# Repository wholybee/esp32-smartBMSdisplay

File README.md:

# esp32-smartBMSdisplay
ESP32 version of JBD BMS display with Bluetooth connection

This is a BMS monitor for JBD and Overkill Solar BMS. It supports bluetooth connection to the BMS, and can alarm prior to BMS disconnect per ABYC recommendation. It is inspired by a project at https://github.com/vagueDirector/ArduinoXiaoxiangSmartBMSDisplay, but bears little resemblance at this point.

This project uses the Overkill Solar library for accessing the BMS, and modifiyed code from https://github.com/avinabmalla/ESP32_BleSerial

I used an ESP32-WROOM. Others might work also. BLE enabled Arduinos will not work. The ESP32 will connect to the first BMS it finds via bluetooth. Button one cycles through screens, and button two silences the alarm if it is triggered.

To use the alarm requires some changes in the BMS programming. There is a parameter for the delay in seconds before the cutoff occurs. Normally this is set very small, to 1 or 2 seconds. This value is how long of a warning you will get before the cutoff occurs. Some versions of the app do not allow this to be set greater than 10 seconds, but using the Overkill Solar app allows higher values.

Care should be taken when selecting the delay value. If an overvoltage or undervoltage situation occurs, there should be no issue waiting 20 or 30 seconds. If an overcurrent situation occurs, you really should not wait to disconnect to allow for an alarm, regardless of what ABYC says. So, I suggest leaving the delay for overcurrent very low, and changing the delay for overvoltage to 20 or 30 seconds.

ESP32 WROOM - https://www.amazon.com/gp/product/B08MQDS6WV/ref=ppx_yo_dt_b_search_asin_title
128x64 OLED screen - https://www.amazon.com/gp/product/B08BRCBKNR/ref=ppx_yo_dt_b_asin_title_o01_s00
Button - https://www.digikey.com/en/products/detail/c-k/KSA0A531-LFTR/5975610?s=N4IgTCBcDaINIGUCCAGJBWAzARgDIDEAVAJQFoA5AERAF0BfIA
Button cap - https://www.digikey.com/en/products/detail/c-k/BTNK0120/498768?s=N4IgTCBcDaICwAYCMBaJYDMBOFA5AIiALoC%2BQA
Buzzer - https://www.amazon.com/gp/product/B07TRK5M2T/ref=ppx_yo_dt_b_search_asin_title

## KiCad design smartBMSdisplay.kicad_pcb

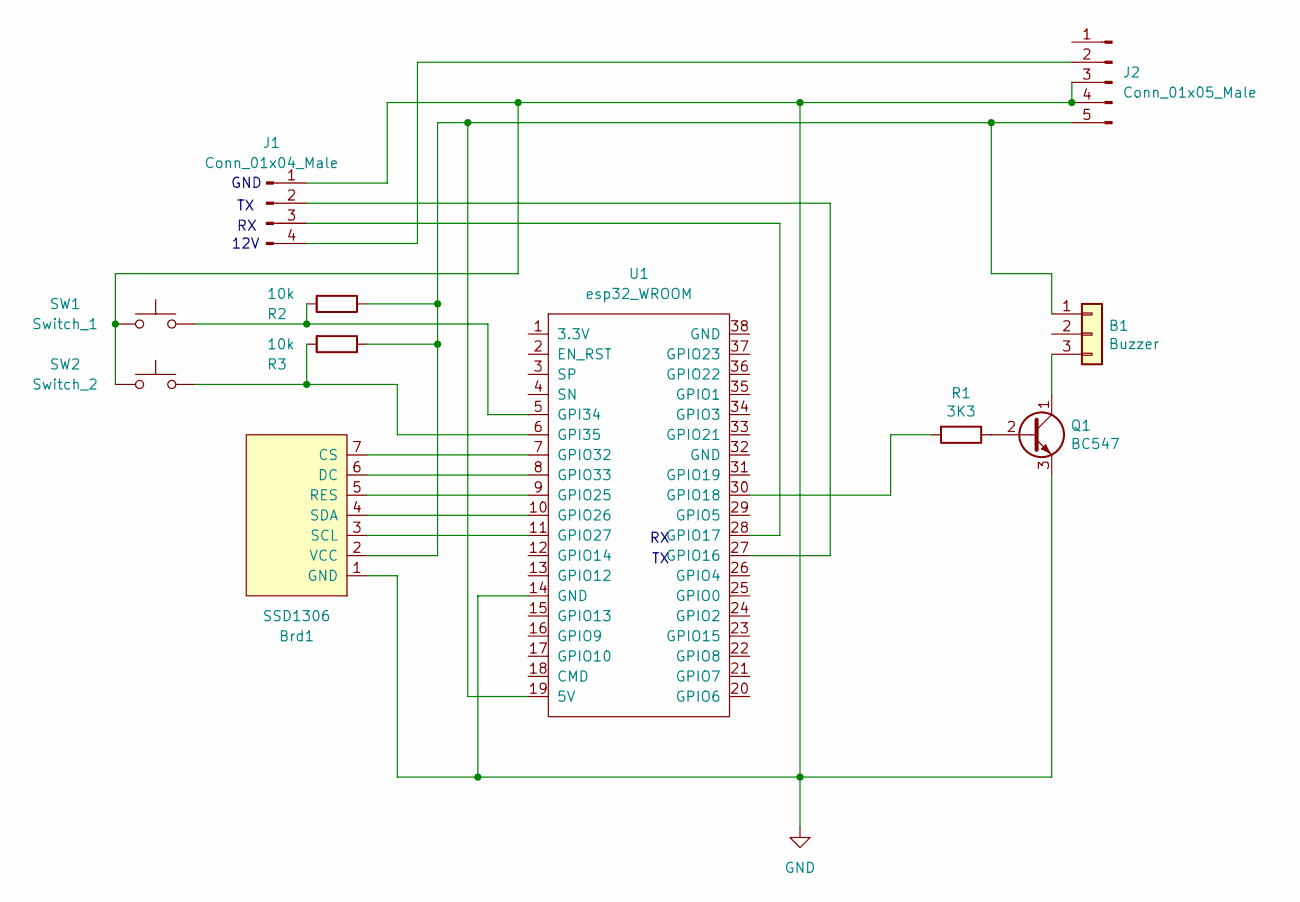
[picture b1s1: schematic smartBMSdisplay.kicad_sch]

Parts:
B1: Buzzer; PinHeader_1x03_P2.00mm_Vertical
Brd1: SSD1306; 128x64OLED
J1: Conn_01x04_Male; PinHeader_1x04_P2.54mm_Vertical
J2: Conn_01x05_Male; PinHeader_1x05_P2.54mm_Vertical
Q1: BC547; TO-92_HandSolder
R1: 3K3; R_Axial_DIN0207_L6.3mm_D2.5mm_P10.16mm_Horizontal
R2, R3: 10k; R_Axial_DIN0207_L6.3mm_D2.5mm_P10.16mm_Horizontal
SW1: Switch_1; SW_Tactile_Straight_KSA0Axx1LFTR
SW2: Switch_2; SW_Tactile_Straight_KSA0Axx1LFTR
U1: esp32_WROOM; ESP32_Devkit_38Pins

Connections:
GND: Brd1.1 (GND), J1.1, J2.3, J2.4, Q1.3 (E), SW1.2, SW2.2, U1.14 (GND)
unnamed: B1.1, Brd1.2 (VCC), J2.5, R2.1, R3.1, U1.19 (5V)
unnamed: B1.3, Q1.1 (C)
unnamed: Brd1.3 (SCL), U1.11 (GPIO27)
unnamed: Brd1.4 (SDA), U1.10 (GPIO26)
unnamed: Brd1.5 (RES), U1.9 (GPIO25)
unnamed: Brd1.6 (DC), U1.8 (GPIO33)
unnamed: Brd1.7 (CS), U1.7 (GPIO32)
unnamed: J1.2, U1.27 (GPIO16)
unnamed: J1.3, U1.28 (GPIO17)
unnamed: J1.4, J2.2
unnamed: Q1.2 (B), R1.1
unnamed: R1.2, U1.30 (GPIO18)
unnamed: R2.2, SW1.1, U1.5 (GPI34)
unnamed: R3.2, SW2.1, U1.6 (GPI35)

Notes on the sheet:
12V
GND

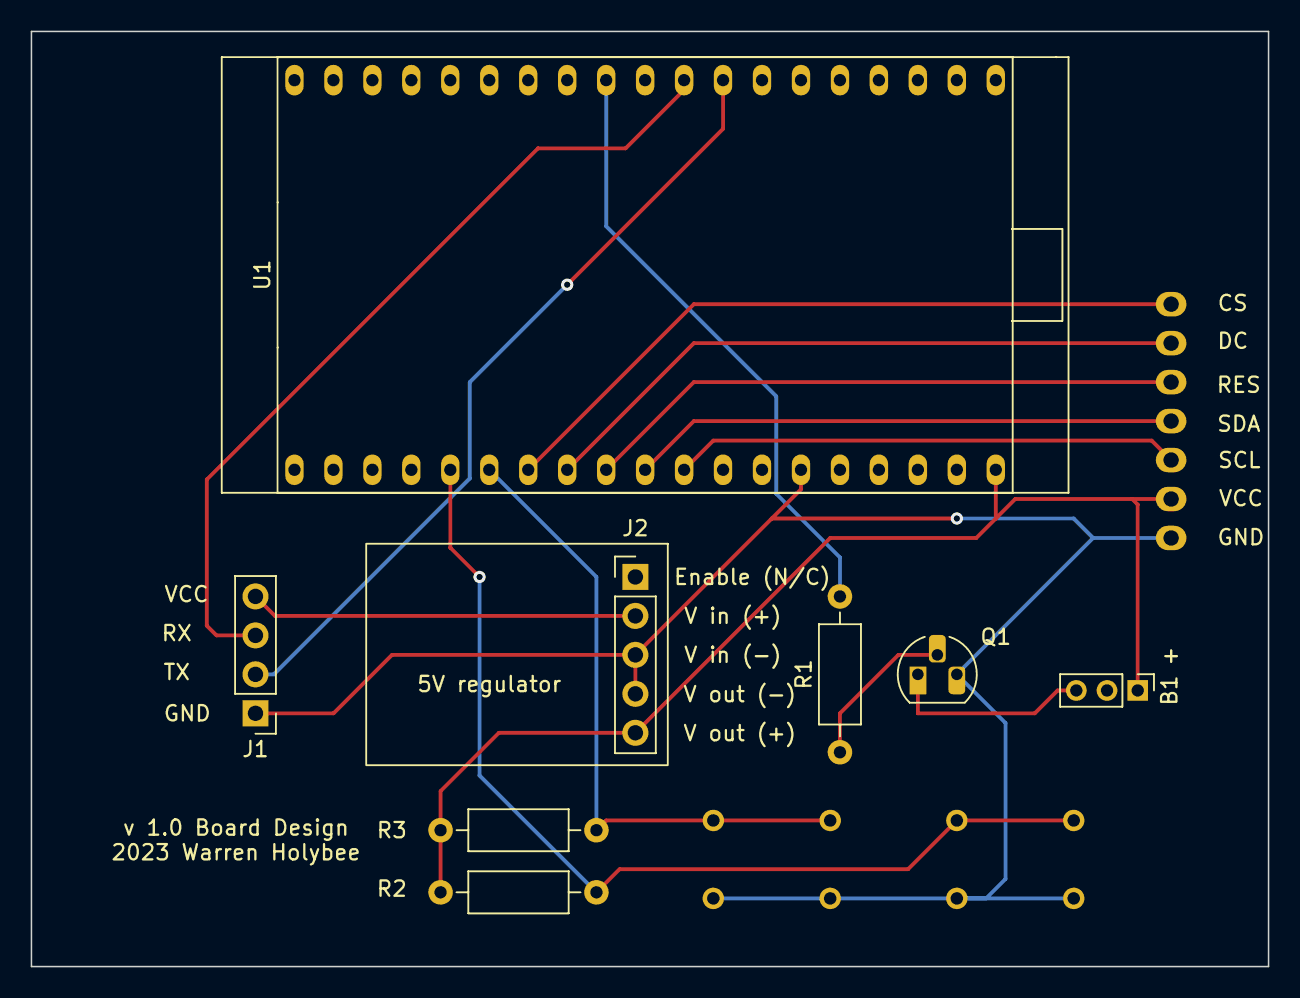
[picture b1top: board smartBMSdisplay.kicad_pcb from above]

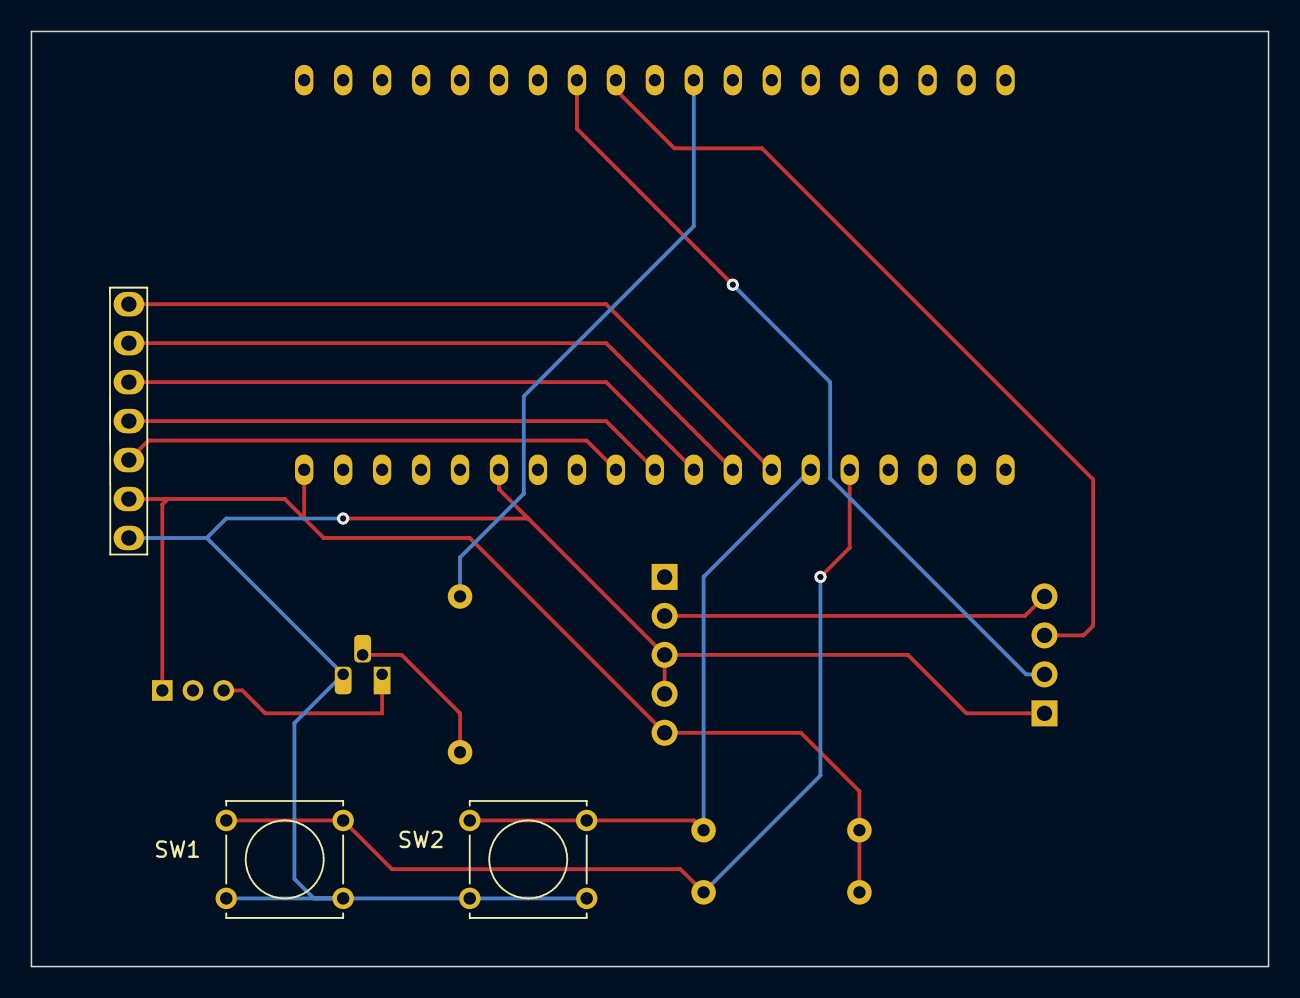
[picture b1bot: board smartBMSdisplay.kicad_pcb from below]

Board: 2 copper layers, 80.6 x 61.0 mm, 11 parts (3 on the bottom side), 15 nets.

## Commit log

2023-03-08 First working bluetooth version
2023-03-29 Update Readme, misc display changes, update PCB
2023-06-01 Various updates
2025-07-28 Update to work with new libraries
